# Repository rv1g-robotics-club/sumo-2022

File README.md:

# RV1G Minisumo

Repozitorija satur RV1G Minisumo robota izstrādes failus.

* firmware - micropython bibliotēkas un programmas pamats robota programmatūrai.
* hardware - robota elektronikas shēma un iespiedplates (PCB) izstrādes projekts

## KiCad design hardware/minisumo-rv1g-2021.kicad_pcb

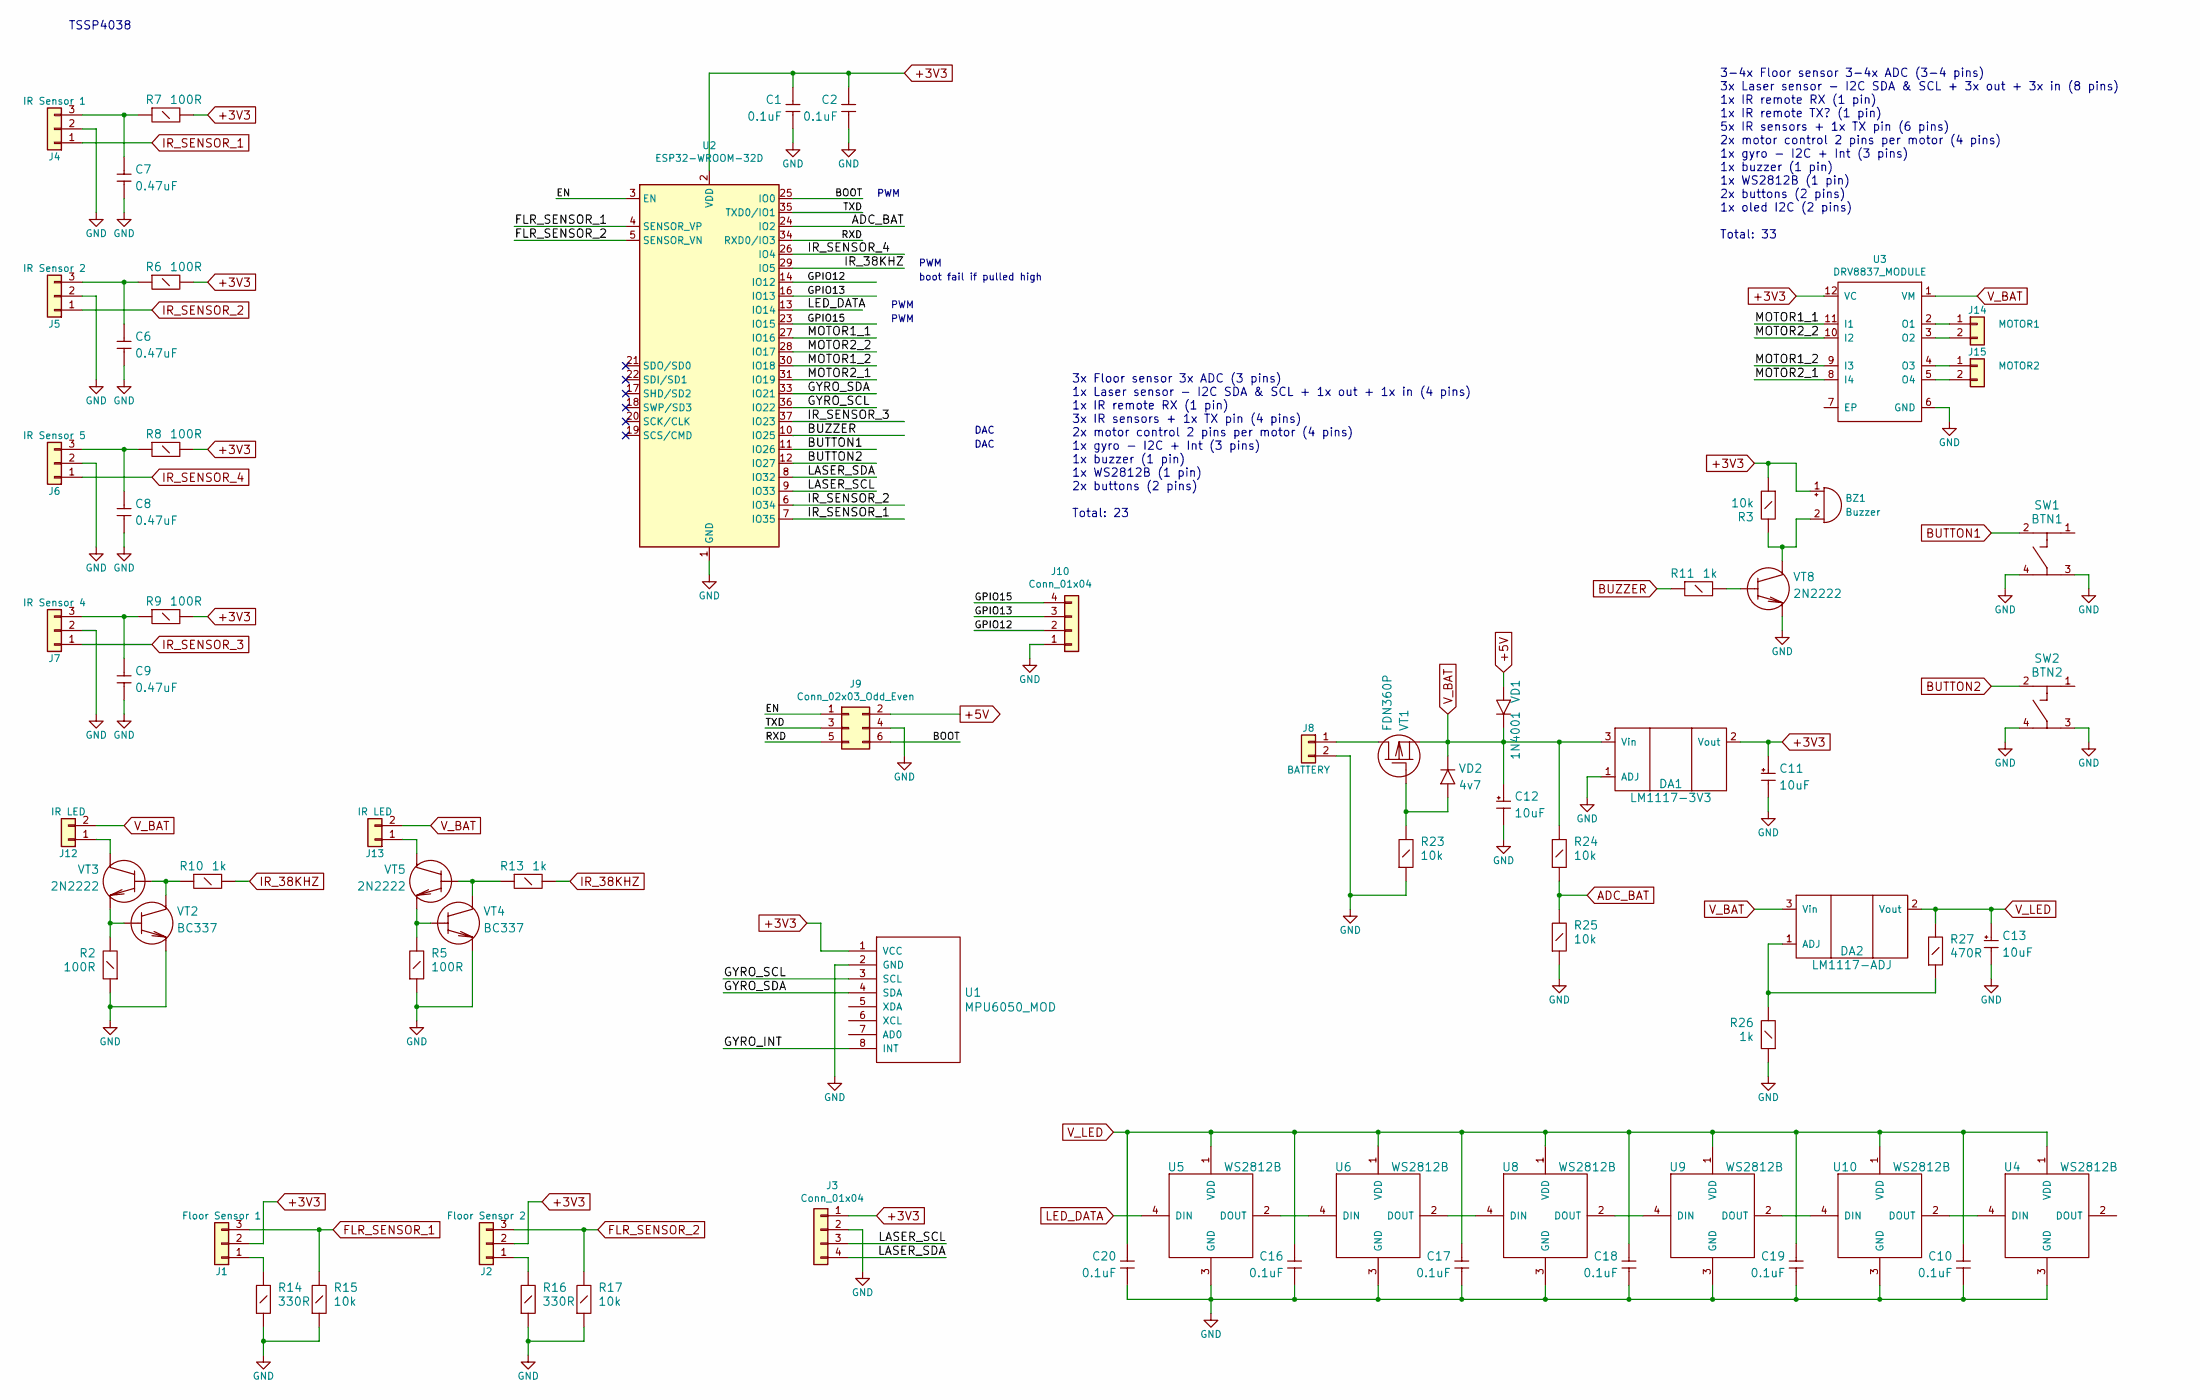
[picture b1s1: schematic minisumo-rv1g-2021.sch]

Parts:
BZ1: Buzzer; Beeper_12xx
C1, C2, C10, C16, C17, C18, C19, C20: 0.1uF; C_Disc_D3.0mm_W1.6mm_P2.50mm
C6, C7, C8, C9: 0.47uF; C-5mm
C11, C12, C13: 10uF; CE63x25
DA1: LM1117-3V3; SOT-223
DA2: LM1117-ADJ; SOT-223
J1: Floor Sensor 1; JST-B3B-ZR
J2: Floor Sensor 2; JST-B3B-ZR
J3: Conn_01x04; JST-B4B-ZR
J4: IR Sensor 1; JST-B3B-ZR
J5: IR Sensor 2; JST-B3B-ZR
J6: IR Sensor 5; JST-B3B-ZR
J7: IR Sensor 4; JST-B3B-ZR
J8: BATTERY; JST_PH_B2B-PH-K_1x02_P2.00mm_Vertical
J9: Conn_02x03_Odd_Even; IDC-Header_2x03_P2.54mm_Vertical
J10: Conn_01x04; PinHeader_1x04_P2.54mm_Vertical
J12, J13: IR LED; JST-B2B-ZR
J14: MOTOR1; JST_PH_B2B-PH-K_1x02_P2.00mm_Vertical
J15: MOTOR2; JST_PH_B2B-PH-K_1x02_P2.00mm_Vertical
R2, R5: 100R; R_W4_THT_Vert
R3, R15, R17, R24, R25: 10k; R_W8_THT_Hor
R6, R7, R8, R9: 100R; R_W8_THT_Hor
R10, R11, R13: 1k; R_W8_THT_Vert
R14, R16: 330R; R_W8_THT_Hor
R23: 10k; R_W8_THT_Vert
R26: 1k; R_W8_THT_Hor
R27: 470R; R_W8_THT_Hor
SW1: BTN1; 6x6_SPST
SW2: BTN2; 6x6_SPST
U1: MPU6050_MOD; MPU6050
U2: ESP32-WROOM-32D; ESP32-WROOM-32
U3: DRV8837_MODULE
U4, U5, U6, U8, U9, U10: WS2812B
VD1: 1N4001; D_DO-41_SOD81_P2.54mm_Vertical_AnodeUp
VD2: 4v7; D_DO-35_SOD27_P2.54mm_Vertical_AnodeUp
VT1: FDN360P; SOT-23
VT2, VT4: BC337; TO-92
VT3, VT5, VT8: 2N2222; TO-92

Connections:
+3V3: BZ1.1 (-), C1.1, C2.1, C11.1, DA1.2 (Vout), J1.2, J2.2, J3.1, R3.1, R6.2, R7.2, R8.2, R9.2, U1.1 (VCC), U2.2 (VDD), U3.12 (VC)
+5V: J9.2, VD1.1 (A)
/BOOT: J9.6, U2.25 (IO0)
/EN: J9.1, U2.3 (EN)
/GPIO12: J10.2, U2.14 (IO12)
/GPIO13: J10.3, U2.16 (IO13)
/GPIO15: J10.4, U2.23 (IO15)
/GYRO_INT: U1.8 (INT)
/GYRO_SCL: U1.3 (SCL), U2.36 (IO22)
/GYRO_SDA: U1.4 (SDA), U2.33 (IO21)
/LASER_SCL: J3.3, U2.9 (IO33)
/LASER_SDA: J3.4, U2.8 (IO32)
/MOTOR1_1: U2.27 (IO16), U3.11 (I1)
/MOTOR1_2: U2.30 (IO18), U3.9 (I3)
/MOTOR2_1: U2.31 (IO19), U3.8 (I4)
/MOTOR2_2: U2.28 (IO17), U3.10 (I2)
/RXD: J9.5, U2.34 (RXD0/IO3)
/TXD: J9.3, U2.35 (TXD0/IO1)
ADC_BAT: R24.1, R25.2, U2.24 (IO2)
BUTTON1: SW1.2, U2.11 (IO26)
BUTTON2: SW2.2, U2.12 (IO27)
BUZZER: R11.1, U2.10 (IO25)
FLR_SENSOR_1: J1.3, R15.2, U2.4 (SENSOR_VP)
FLR_SENSOR_2: J2.3, R17.2, U2.5 (SENSOR_VN)
GND: C1.2, C2.2, C6.2, C7.2, C8.2, C9.2, C10.2, C11.2, C12.2, C13.2, C16.2, C17.2, C18.2, C19.2, C20.2, DA1.1 (ADJ), J3.2, J4.2, J5.2, J6.2, J7.2, J8.2, J9.4, J10.1, R2.1, R5.1, R14.1, R15.1, R16.1, R17.1, R23.1, R25.1, R26.1, SW1.3, SW1.4, SW2.3, SW2.4, U1.2 (GND), U2.1 (GND), U2.15 (GND), U2.38 (GND), U2.39 (GND), U3.6 (GND), U4.3 (GND), U5.3 (GND), U6.3 (GND), U8.3 (GND), U9.3 (GND), U10.3 (GND), VT2.3 (E), VT4.3 (E), VT8.3 (E)
IR_38KHZ: R10.2, R13.2, U2.29 (IO5)
IR_SENSOR_1: J4.1, U2.7 (IO35)
IR_SENSOR_2: J5.1, U2.6 (IO34)
IR_SENSOR_3: J7.1, U2.37 (IO23)
IR_SENSOR_4: J6.1, U2.26 (IO4)
LED_DATA: U2.13 (IO14), U5.4 (DIN)
unnamed: BZ1.2 (+), R3.2, VT8.1 (K)
unnamed: C6.1, J5.3, R6.1
unnamed: C7.1, J4.3, R7.1
unnamed: C8.1, J6.3, R8.1
unnamed: C9.1, J7.3, R9.1
unnamed: DA2.1 (ADJ), R26.2, R27.1
unnamed: J1.1, R14.2
unnamed: J2.1, R16.2
unnamed: J8.1, VT1.3 (D)
unnamed: J12.1, VT3.1 (K)
unnamed: J13.1, VT5.1 (K)
unnamed: J14.1, U3.2 (O1)
unnamed: J14.2, U3.3 (O2)
unnamed: J15.1, U3.4 (O3)
unnamed: J15.2, U3.5 (O4)
unnamed: R2.2, VT2.2 (B), VT3.3 (E)
unnamed: R5.2, VT4.2 (B), VT5.3 (E)
unnamed: R10.1, VT2.1 (K), VT3.2 (B)
unnamed: R11.2, VT8.2 (B)
unnamed: R13.1, VT4.1 (K), VT5.2 (B)
unnamed: R23.2, VD2.1 (A), VT1.1 (G)
unnamed: U5.2 (DOUT), U6.4 (DIN)
unnamed: U6.2 (DOUT), U8.4 (DIN)
unnamed: U8.2 (DOUT), U9.4 (DIN)
unnamed: U4.4 (DIN), U10.2 (DOUT)
unnamed: U9.2 (DOUT), U10.4 (DIN)
V_BAT: C12.1, DA1.3 (Vin), DA2.3 (Vin), J12.2, J13.2, R24.2, U3.1 (VM), VD1.2 (K), VD2.2 (K), VT1.2 (S)
V_LED: C10.1, C13.1, C16.1, C17.1, C18.1, C19.1, C20.1, DA2.2 (Vout), R27.2, U4.1 (VDD), U5.1 (VDD), U6.1 (VDD), U8.1 (VDD), U9.1 (VDD), U10.1 (VDD)

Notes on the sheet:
3-4x Floor sensor 3-4x ADC (3-4 pins) 3x Laser sensor - I2C SDA & SCL + 3x out + 3x in (8 pins) 1x IR remote RX (1 pin) 1x IR remote TX? (1 pin) 5x IR sensors + 1x TX pin (6 pins) 2x motor control 2 pins per motor (4 pins) 1x gyro - I2C + Int (3 pins) 1x buzzer (1 pin) 1x WS2812B (1 pin) 2x buttons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
TSSP4038
3x Floor sensor 3x ADC (3 pins) 1x Laser sensor - I2C SDA & SCL + 1x out + 1x in (4 pins) 1x IR remote RX (1 pin) 3x IR sensors + 1x TX pin (4 pins) 2x motor control 2 pins per motor (4 pins) 1x gyro - I2C + Int (3 pins) 1x buzzer (1 pin) 1x WS2812B (1 pin) 2x buttons (2 pins) Total: 23
PWM
boot fail if pulled high
DAC

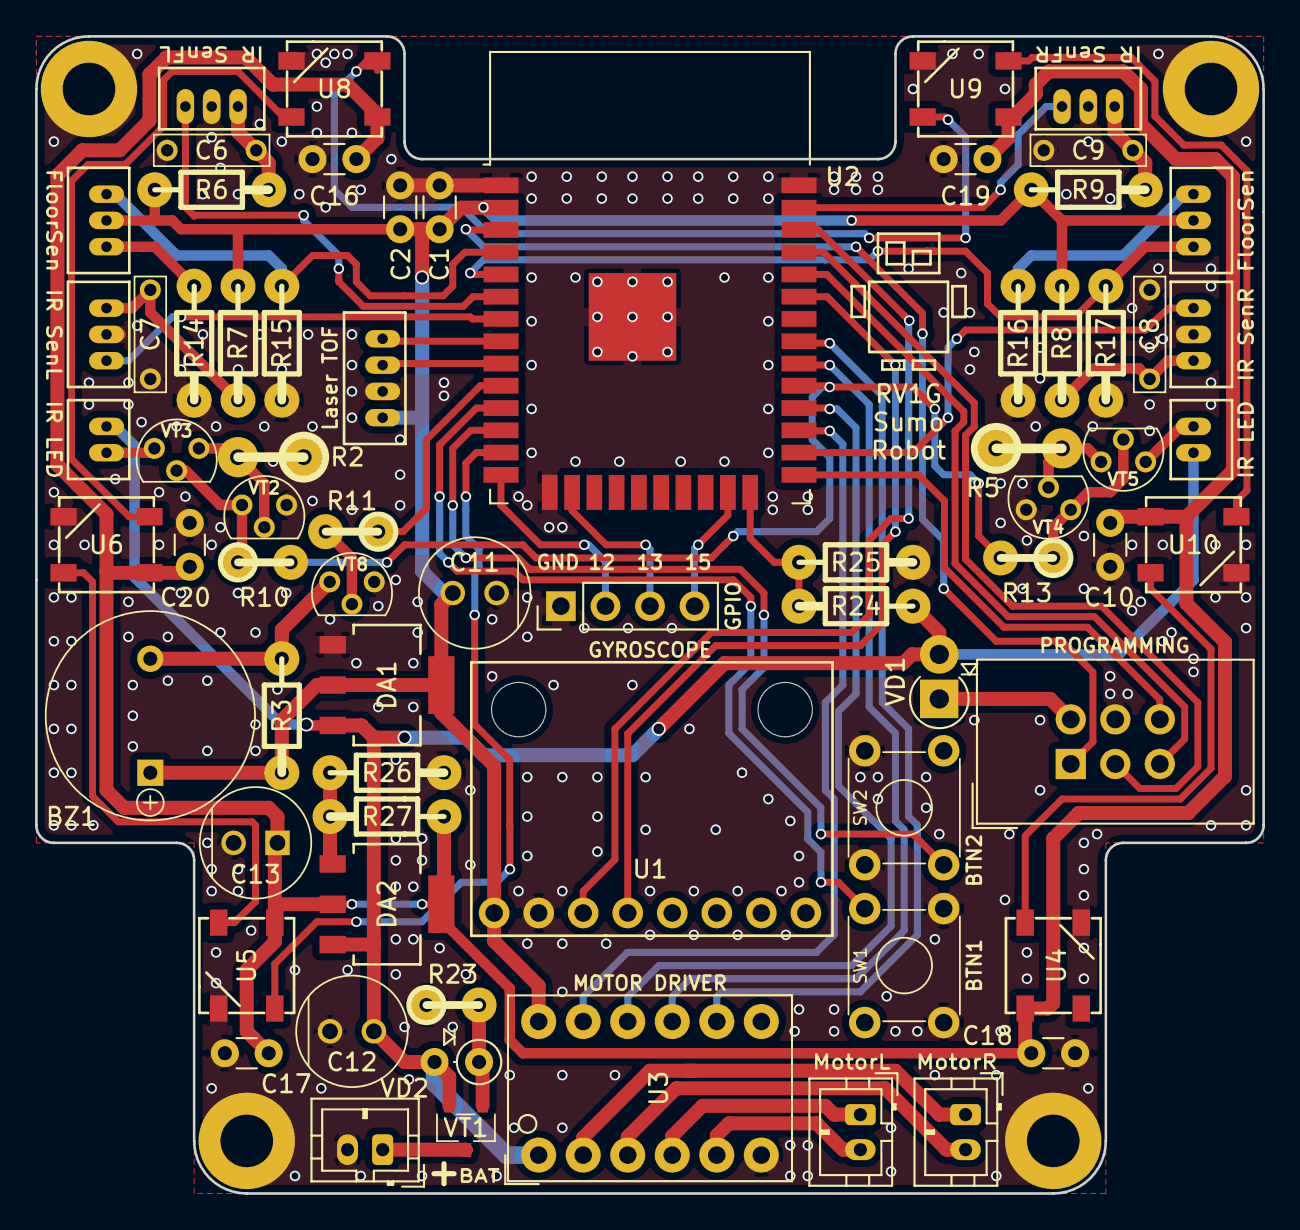
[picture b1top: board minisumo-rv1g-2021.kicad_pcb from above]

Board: 2 copper layers, 70.0 x 66.0 mm, 74 parts (0 on the bottom side), 58 nets.

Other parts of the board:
X**: 1PIN
X**#2, X**#3, X**#4: 1PIN

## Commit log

2023-04-12 Added Hardware
2023-04-12 Added main and firmware README
2023-04-12 Updated firmware README
